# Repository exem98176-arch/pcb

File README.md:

# pcb
MY first pcb
this is my first pcb attempt done by me to learn the proccess
It is a crab/ spider design I  made to be a little key chain with button control leds
this was my adventure of ki cad and learning the basics

Pho

AI USAGE
cluade check my conection and helped teach me WORK AND IDEAS ARE MINE AND MINE ALONE

I am a fellow reviewer so most free time goes to thaat so please accept
I have full file

STEPS to recreate
send zip to jlpcb(or whatever)
solder parts 

BOM
4 leds (standard size)
3 buttons(standard size) 
3v coin cell battery
CR2032 button battery holder

Ping me @seb sev

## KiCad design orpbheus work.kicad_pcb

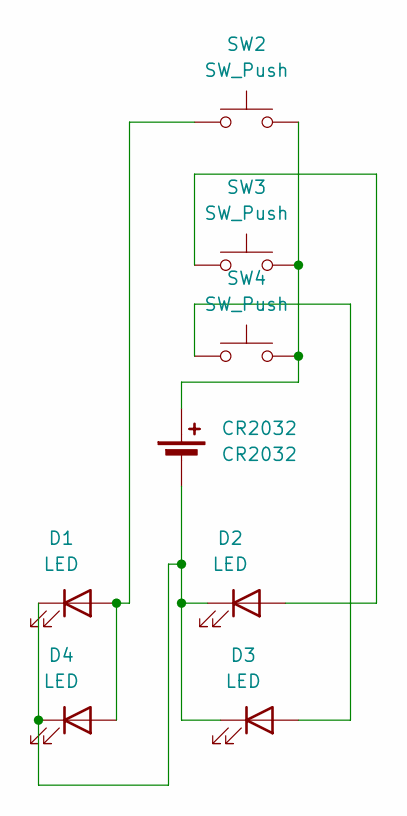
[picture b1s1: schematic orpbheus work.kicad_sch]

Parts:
CR2032: CR2032; BatteryHolder_Keystone_3002_1x2032
D1, D2, D3, D4: LED; LED_D3.0mm
SW2, SW3, SW4: SW_Push; SW_PUSH_6mm_H4.3mm

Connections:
unnamed: CR2032.1 (+), SW2.2, SW3.2, SW4.2
unnamed: CR2032.2 (-), D1.1 (K), D2.1 (K), D3.1 (K), D4.1 (K)
unnamed: D1.2 (A), D4.2 (A), SW2.1
unnamed: D2.2 (A), SW3.1
unnamed: D3.2 (A), SW4.1

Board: 2 copper layers, 8 parts (0 on the bottom side), 5 nets, no tracks yet.
